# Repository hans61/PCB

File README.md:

# PCB
Gigatron extensions
=======================
Here I collect my PCB (Eagle + Gerber) extensions for the Gigatron TTL computer. You can find the original project here:
https://gigatron.io/

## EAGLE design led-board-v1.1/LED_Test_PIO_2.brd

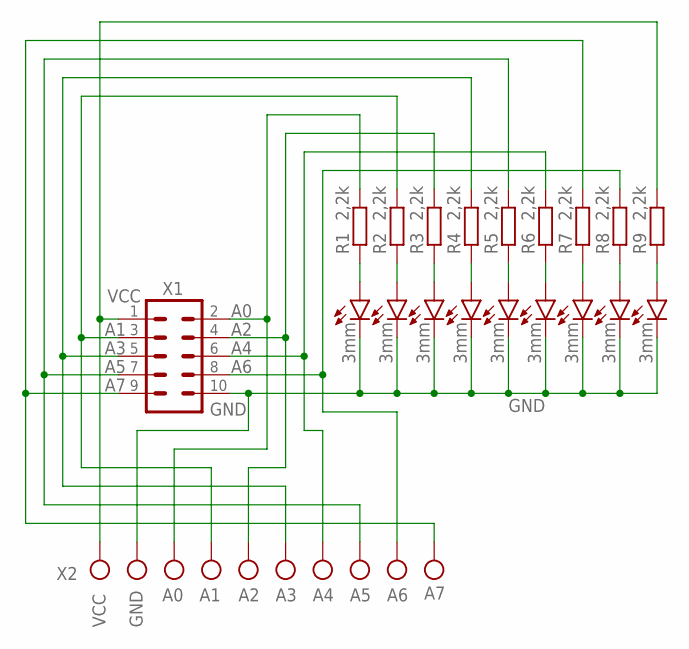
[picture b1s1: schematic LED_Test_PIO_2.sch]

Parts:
LED1, LED2, LED3, LED4, LED5, LED6, LED7, LED8, LED9: 3mm; LED3MM
R1, R2, R3, R4, R5, R6, R7, R8, R9: 2,2k; 0207/10
SV1: X1; ML10
X1, X2, X3, X4, X5: X2; W237-102

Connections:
A0: R1.2, SV1.2, X2.1
A1: R2.2, SV1.3, X2.2
A2: R3.2, SV1.4, X3.1
A3: R4.2, SV1.5, X3.2
A4: R6.2, SV1.6, X4.1
A5: R5.2, SV1.7, X4.2
A6: R8.2, SV1.8, X5.1
A7: R7.2, SV1.9, X5.2
GND: LED1.K (C), LED2.K (C), LED3.K (C), LED4.K (C), LED5.K (C), LED6.K (C), LED7.K (C), LED8.K (C), LED9.K (C), SV1.10, X1.2
unnamed: LED1.A, R1.1
unnamed: LED2.A, R2.1
unnamed: LED3.A, R3.1
unnamed: LED4.A, R4.1
unnamed: LED5.A, R5.1
unnamed: LED6.A, R6.1
unnamed: LED7.A, R7.1
unnamed: LED8.A, R8.1
unnamed: LED9.A, R9.1
VCC: R9.2, SV1.1, X1.1

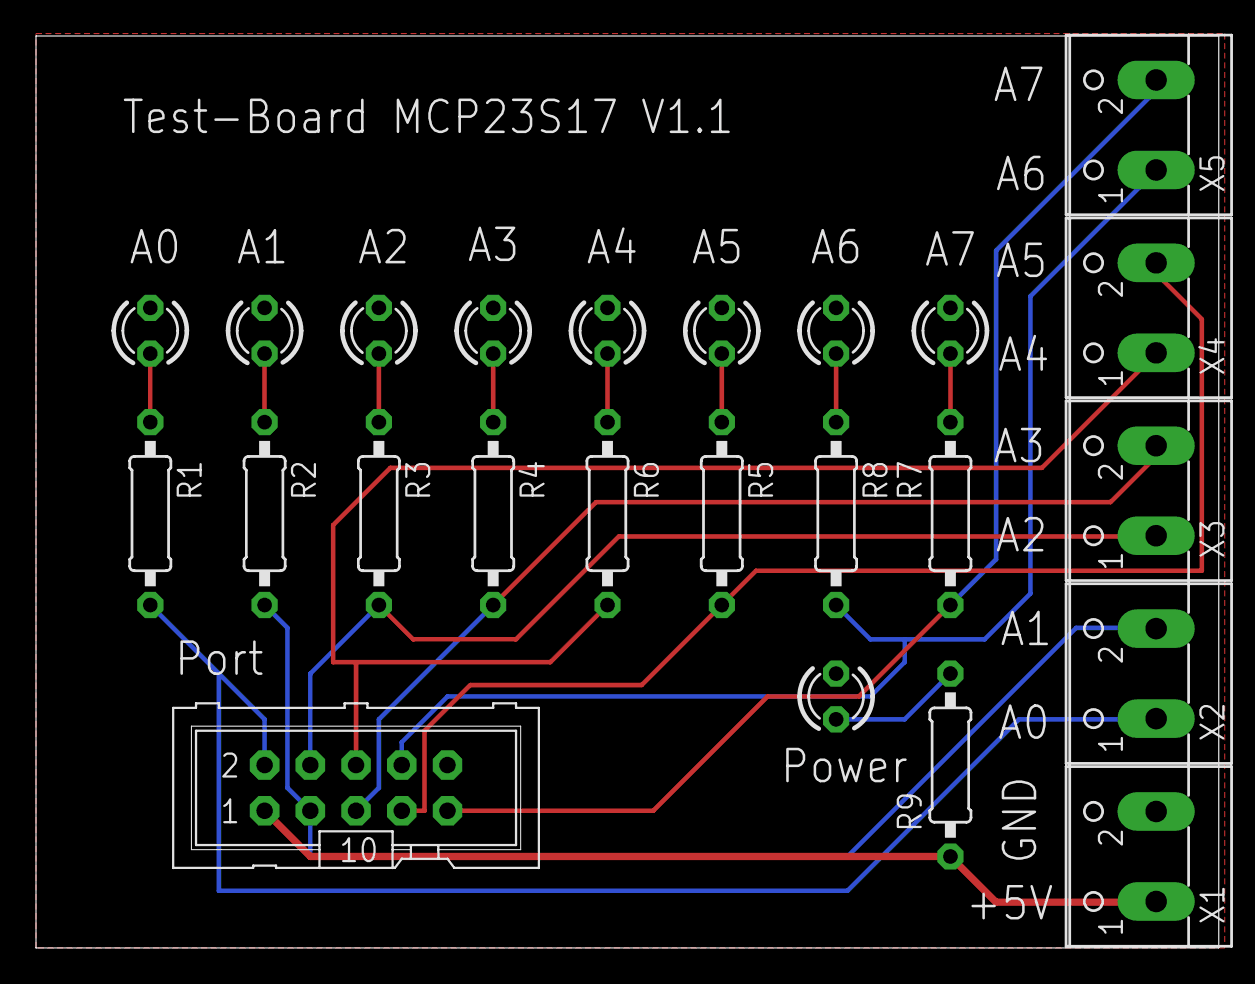
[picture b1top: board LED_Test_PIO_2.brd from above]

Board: 2 copper layers, 65.7 x 50.7 mm, 24 parts (0 on the bottom side), 19 nets.

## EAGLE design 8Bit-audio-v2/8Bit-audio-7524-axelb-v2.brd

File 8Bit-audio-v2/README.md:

8 Bit Audo with the TLC7524
===========================

It is the second draft that tries to avoid the mistakes of the first version. The connection to VREF (15) has been changed. The pin header was adapted to the PCB of lb3361. This means that a 1 to 1 cable can be used. Component footprints have been improved.
! This is just a draft.

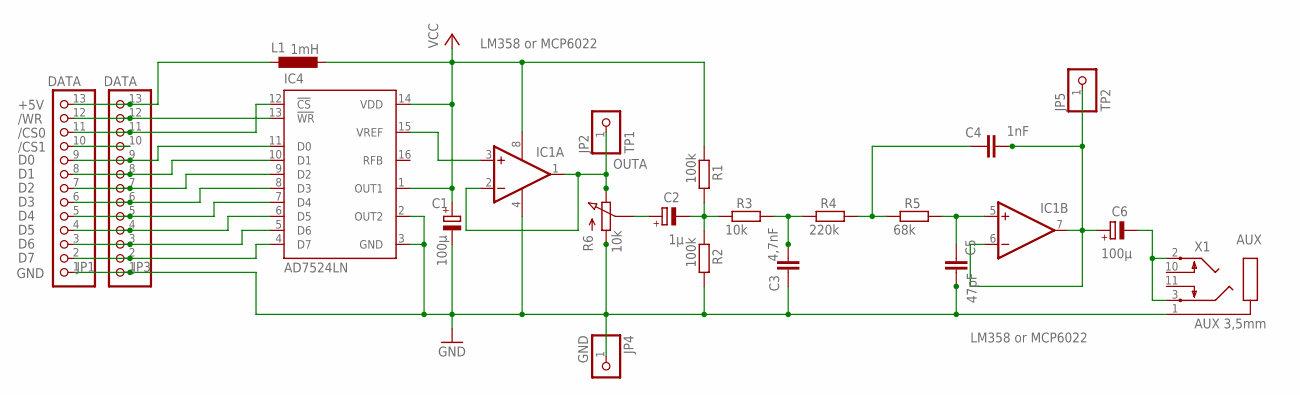
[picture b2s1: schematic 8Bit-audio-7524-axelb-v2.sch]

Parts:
C1, C6: 100µ; E5-5
C2: 1µ; E5-5
C3: 4,7nF; RCL_C025_050-055X075
C4: 1nF; RCL_C025_050-055X075
C5: 47pF; RCL_C025_050-055X075
IC1: LM358 or MCP6022; DIL08
IC4: AD7524LN; DIL16
JP1, JP3: DATA; 1X13
JP2: TP1; 1X01
JP4: GND; 1X01
JP5: TP2; 1X01
L1: 1mH; 0207/10
R1, R2: 100k; 0207/10
R3: 10k; 0207/10
R4: 220k; 0207/10
R5: 68k; 0207/10
R6: 10k; POT_3RP/1610N
X1: AUX 3,5mm; SJ1-352XN

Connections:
+5V: JP1.13, JP3.13, L1.1
/CS0: IC4.12 (!CS), JP1.11, JP3.11
/CS1: JP1.10, JP3.10
/WR: IC4.13 (!WR), JP1.12, JP3.12
AUX: C6.-, X1.2, X1.3
D0: IC4.11 (D0), JP1.9, JP3.9
D1: IC4.10 (D1), JP1.8, JP3.8
D2: IC4.9 (D2), JP1.7, JP3.7
D3: IC4.8 (D3), JP1.6, JP3.6
D4: IC4.7 (D4), JP1.5, JP3.5
D5: IC4.6 (D5), JP1.4, JP3.4
D6: IC4.5 (D6), JP1.3, JP3.3
D7: IC4.4 (D7), JP1.2, JP3.2
GND: C1.-, C3.1 (A1), C5.2 (B1), C5.3 (B2), IC1.4 (V-), IC4.2 (OUT2), IC4.3 (GND), JP1.1, JP3.1, JP4.1, R2.2, R6.A1, R6.A2, X1.1
unnamed: C2.-, R1.2, R2.1, R3.1
unnamed: C2.+, R6.M (S)
unnamed: C3.2 (B1), C3.3 (B2), R3.2, R4.1
unnamed: C4.1 (A1), R4.2, R5.1
unnamed: C5.1 (A1), IC1.5 (+IN), R5.2
OUTA: IC1.1 (OUT), IC1.2 (-IN), JP2.1, R6.E1, R6.E2
OUTB: C4.2 (B1), C4.3 (B2), C6.+, IC1.6 (-IN), IC1.7 (OUT), JP5.1
VCC: C1.+, IC1.8 (V+), IC4.1 (OUT1), IC4.14 (VDD), L1.2, R1.1
VREF: IC1.3 (+IN), IC4.15 (VREF)

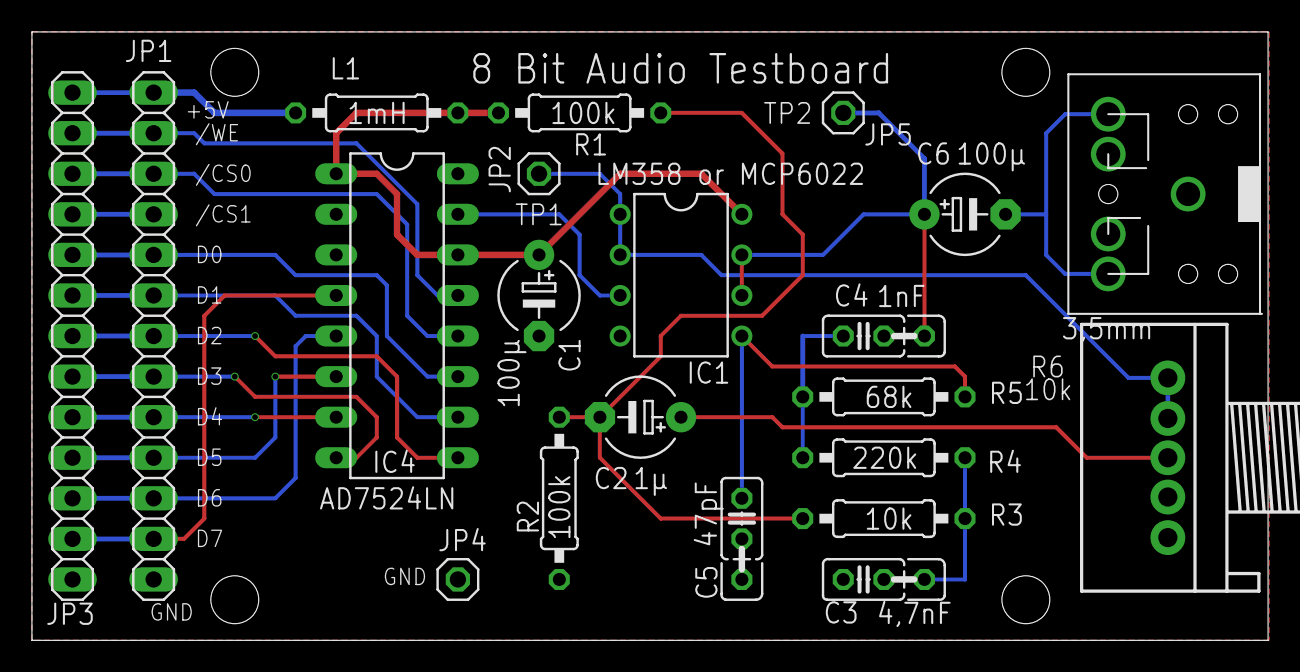
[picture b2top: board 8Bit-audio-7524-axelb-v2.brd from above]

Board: 2 copper layers, 77.4 x 38.1 mm, 21 parts (0 on the bottom side), 23 nets.

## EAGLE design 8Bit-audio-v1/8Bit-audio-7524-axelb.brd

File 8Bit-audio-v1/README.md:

8 Bit Audo with the TLC7524
===========================
This is a small circuit board to test 8 bit audio on the Gigatron. The schematic is from Axelb, thank you very much. Unfortunately I made a mistake. Pin 3 of the MCP6022 is connected to RFB (16). The connection must be separated and a wire must be soldered to VREF (15).
To test the DAC, I first connected it to an Arduino Uno. With the Gigatron it can be connected to the new expansion v7 of lb3361. Many thanks to lb3361 for his work. The following connections must be established:

|Expansion|TLC7524|
|-----------|-----------|
|VCC|+5V|
|/AUXCTRL|/WR|
|/AUXDEV0|/CS|
|A8-A15|D0-D7|
|GND|GND|

In order for the TLC7524 to accept the data, the /WR of GAL1 must be negated.
I changed line 65:

`DEVCLKOUT = !(OE & WE & SPECIALCODE);`

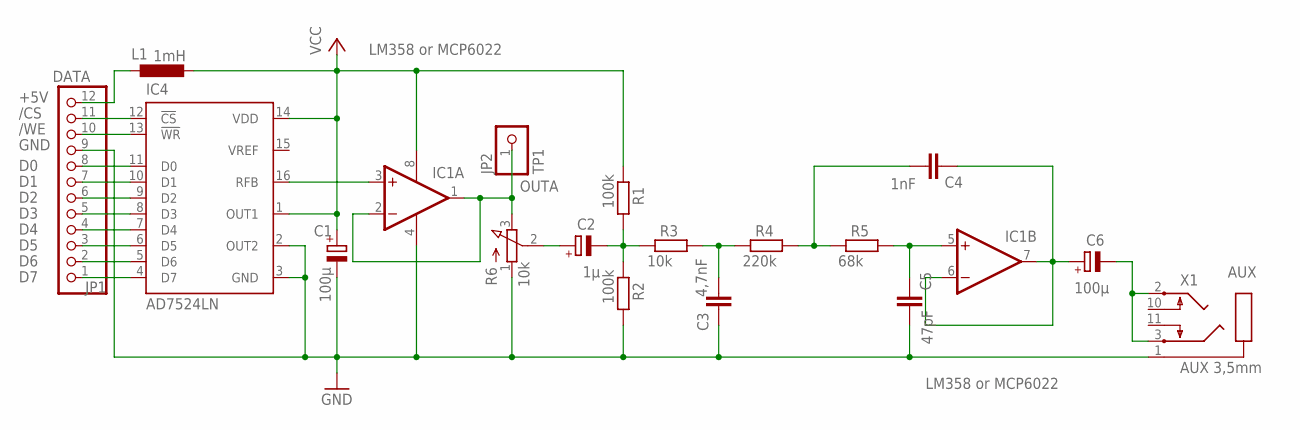
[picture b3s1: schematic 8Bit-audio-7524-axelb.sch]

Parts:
C1, C6: 100µ; E5-5
C2: 1µ; E5-5
C3: 4,7nF; C075-032X103
C4: 1nF; C075-032X103
C5: 47pF; C075-032X103
IC1: LM358 or MCP6022; DIL08
IC4: AD7524LN; DIL16
JP1: DATA; 1X12
JP2: TP1; 1X01
L1: 1mH; 0207/10
R1, R2: 100k; 0207/10
R3: 10k; 0207/10
R4: 220k; 0207/10
R5: 68k; 0207/10
R6: 10k; 3RP/1610N
X1: AUX 3,5mm; SJ1-352XN

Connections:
+5V: JP1.12, L1.1
/CS: IC4.12 (!CS), JP1.11
/WE: IC4.13 (!WR), JP1.10
AUX: C6.-, X1.2, X1.3
D0: IC4.11 (D0), JP1.8
D1: IC4.10 (D1), JP1.7
D2: IC4.9 (D2), JP1.6
D3: IC4.8 (D3), JP1.5
D4: IC4.7 (D4), JP1.4
D5: IC4.6 (D5), JP1.3
D6: IC4.5 (D6), JP1.2
D7: IC4.4 (D7), JP1.1
GND: C1.-, C3.1, C5.2, IC1.4 (V-), IC4.2 (OUT2), IC4.3 (GND), JP1.9, R2.2, R6.1 (A), X1.1
unnamed: IC1.3 (+IN), IC4.16 (RFB)
unnamed: C2.-, R1.2, R2.1, R3.1
unnamed: C2.+, R6.2 (S)
unnamed: C3.2, R3.2, R4.1
unnamed: C4.2, R4.2, R5.1
unnamed: C5.1, IC1.5 (+IN), R5.2
OUTA: IC1.1 (OUT), IC1.2 (-IN), JP2.1, R6.3 (E)
OUTB: C4.1, C6.+, IC1.6 (-IN), IC1.7 (OUT)
VCC: C1.+, IC1.8 (V+), IC4.1 (OUT1), IC4.14 (VDD), L1.2, R1.1

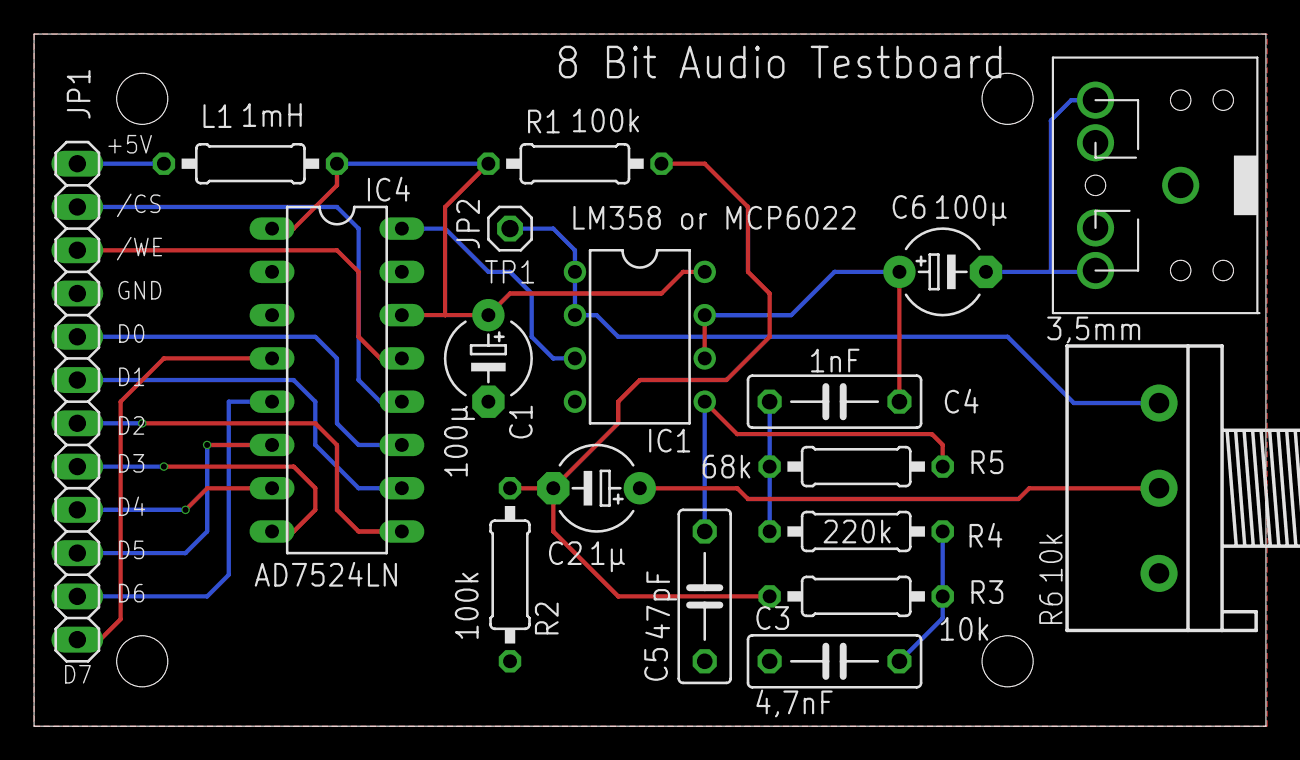
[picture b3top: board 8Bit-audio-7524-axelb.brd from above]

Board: 2 copper layers, 72.3 x 40.6 mm, 18 parts (0 on the bottom side), 22 nets.

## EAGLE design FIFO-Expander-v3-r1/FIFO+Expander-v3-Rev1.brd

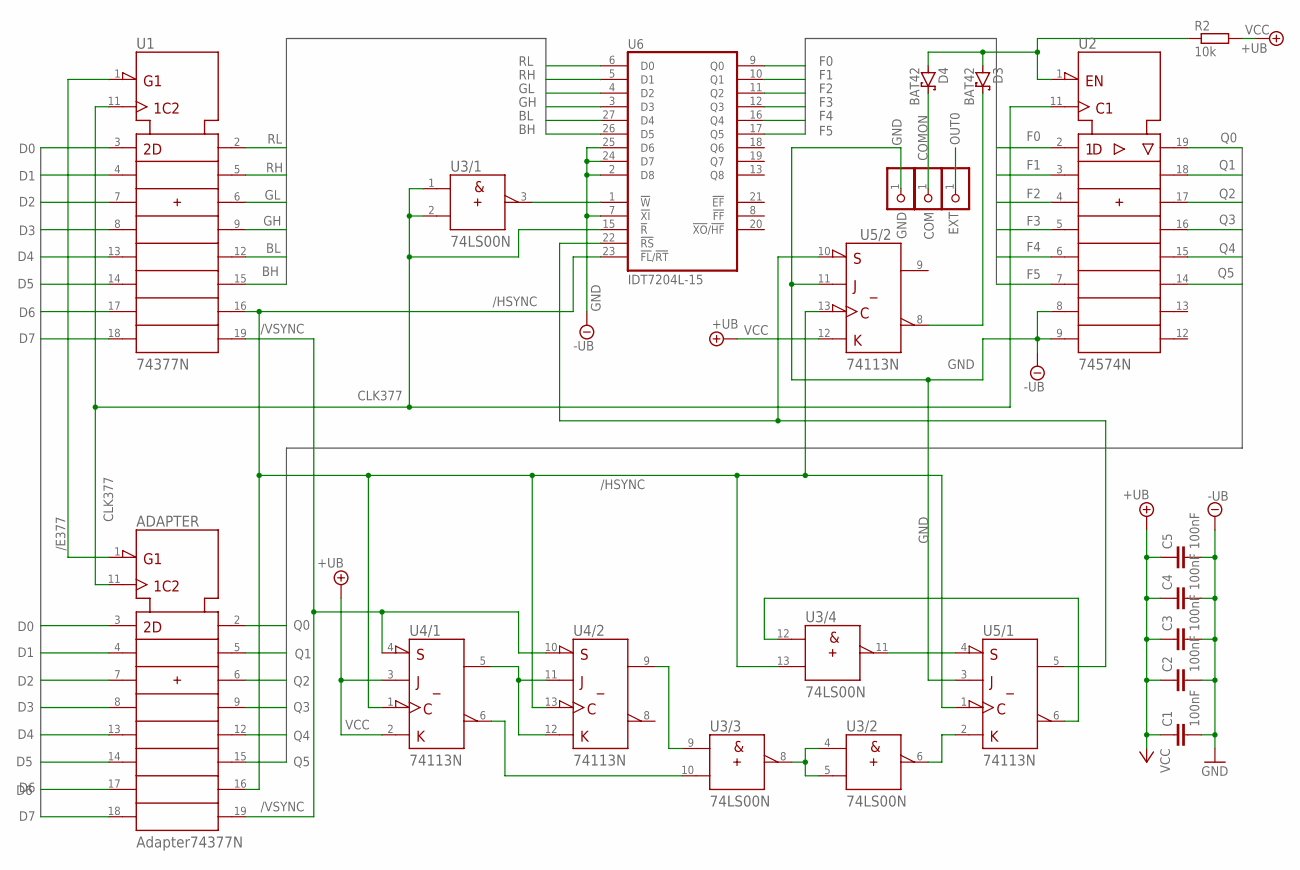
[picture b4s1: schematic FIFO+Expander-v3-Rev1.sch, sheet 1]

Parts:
ADAPTER: Adapter74377N; DIL20
C1, C2, C3, C4, C5: 100nF; C5B2.5
COMON: COM; 1X01
D3, D4: BAT42; DO35-10
GND: GND; 1X01
OUT0: EXT; 1X01
R2: 10k; 0207/10
U1: 74377N; DIL20
U2: 74574N; DIL20
U3: 74LS00N; DIL14
U4, U5: 74113N; DIL14
U6: IDT7204L-15; DIL28-3

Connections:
/E377: ADAPTER.1 (!G), U1.1 (!G)
/HSYNC: ADAPTER.16 (7Q), U1.16 (7Q), U3.13 (B), U4.1 (CLK), U4.13 (CLK), U5.1 (CLK), U5.13 (CLK), U6.23 (!FL!/!RT)
/VSYNC: ADAPTER.19 (8Q), U1.19 (8Q), U4.4 (!PRE), U4.10 (!PRE)
BH: U1.15 (6Q), U6.26 (D5)
BL: U1.12 (5Q), U6.27 (D4)
CLK377: ADAPTER.11 (CLK), U1.11 (CLK), U2.11 (CLK), U3.1 (A), U3.2 (B), U6.15 (!R)
D0: ADAPTER.3 (1D), U1.3 (1D)
D1: ADAPTER.4 (2D), U1.4 (2D)
D2: ADAPTER.7 (3D), U1.7 (3D)
D3: ADAPTER.8 (4D), U1.8 (4D)
D4: ADAPTER.13 (5D), U1.13 (5D)
D5: ADAPTER.14 (6D), U1.14 (6D)
D6: ADAPTER.17 (7D), U1.17 (7D)
D7: ADAPTER.18 (8D), U1.18 (8D)
F0: U2.2 (1D), U6.9 (Q0)
F1: U2.3 (2D), U6.10 (Q1)
F2: U2.4 (3D), U6.11 (Q2)
F3: U2.5 (4D), U6.12 (Q3)
F4: U2.6 (5D), U6.16 (Q4)
F5: U2.7 (6D), U6.17 (Q5)
GH: U1.9 (4Q), U6.3 (D3)
GL: U1.6 (3Q), U6.4 (D2)
GND: ADAPTER.10 (-UB), C1.2, C2.2, C3.2, C4.2, C5.2, GND.1, U1.10 (-UB), U2.8 (7D), U2.9 (8D), U2.10 (-UB), U3.7 (-UB), U4.7 (-UB), U5.3 (J), U5.7 (-UB), U5.11 (J), U6.2 (D8), U6.7 (!XI), U6.14 (GND), U6.24 (D7), U6.25 (D6); also elsewhere on the board
unnamed: U4.5 (Q), U4.11 (J), U4.12 (K)
unnamed: U3.3 (Y), U6.1 (!W)
unnamed: U3.10 (B), U4.6 (!Q)
unnamed: U3.9 (A), U4.9 (Q)
unnamed: D3.A, D4.A, R2.1, U2.1 (!OC)
unnamed: U3.4 (A), U3.5 (B), U3.8 (Y)
unnamed: U3.6 (Y), U5.2 (K)
unnamed: U3.11 (Y), U5.4 (!PRE)
unnamed: U3.12 (A), U5.6 (!Q)
unnamed: COMON.1, D4.C
unnamed: D3.C, U5.8 (!Q)
unnamed: U5.5 (Q), U5.10 (!PRE), U6.22 (!RS)
OUT0: OUT0.1; also elsewhere on the board
Q0: ADAPTER.2 (1Q), U2.19 (1Q)
Q1: ADAPTER.5 (2Q), U2.18 (2Q)
Q2: ADAPTER.6 (3Q), U2.17 (3Q)
Q3: ADAPTER.9 (4Q), U2.16 (4Q)
Q4: ADAPTER.12 (5Q), U2.15 (5Q)
Q5: ADAPTER.15 (6Q), U2.14 (6Q)
RH: U1.5 (2Q), U6.5 (D1)
RL: U1.2 (1Q), U6.6 (D0)
VCC: ADAPTER.20 (+UB), C1.1, C2.1, C3.1, C4.1, C5.1, R2.2, U1.20 (+UB), U2.20 (+UB), U3.14 (+UB), U4.2 (K), U4.3 (J), U4.14 (+UB), U5.12 (K), U5.14 (+UB), U6.28 (VCC); also elsewhere on the board

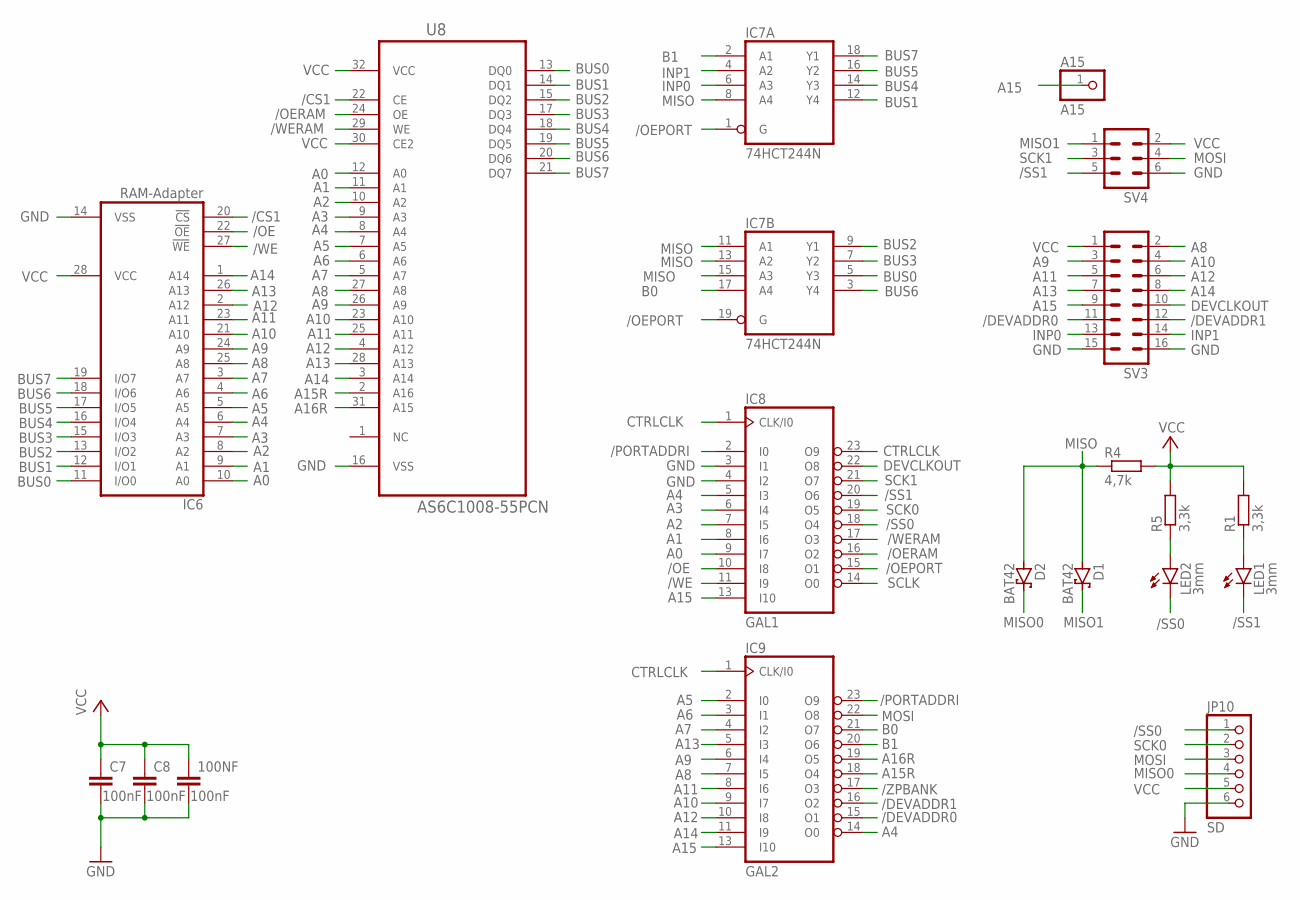
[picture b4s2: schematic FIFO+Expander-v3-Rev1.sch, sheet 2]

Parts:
100NF: 100nF; C5B2.5
A15: A15; 1X01
C7, C8: 100nF; C5B2.5
D1, D2: BAT42; DO35-10
IC6: RAM-Adapter; DIL28-6
IC7: 74HCT244N; DIL20
IC8: GAL1; DIL24-3
IC9: GAL2; DIL24-3
JP10: SD; 1X06
LED1, LED2: 3mm; LED3MM
R1, R5: 3,3k; 0207/10
R4: 4,7k; 0207/10
SV3: ML16
SV4: ML6
U8: AS6C1008-55PCN; DIP254P1524X393-32

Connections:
/CS1: IC6.20 (!CS), U8.22 (CE)
/DEVADDR0: IC9.15 (O1), SV3.11; also elsewhere on the board
/DEVADDR1: IC9.16 (O2), SV3.12
/OE: IC6.22 (!OE), IC8.10 (I8)
/OEPORT: IC7.1 (G), IC7.19 (G), IC8.15 (O1)
/OERAM: IC8.16 (O2), U8.24 (OE)
/PORTADDRI: IC8.2 (I0), IC9.23 (O9)
/SS0: IC8.18 (O4), JP10.1, LED2.K (C)
/SS1: IC8.20 (O6), LED1.K (C), SV4.5
/WE: IC6.27 (!WE), IC8.11 (I9)
/WERAM: IC8.17 (O3), U8.29 (WE)
/ZPBANK: IC9.17 (O3)
A0: IC6.10 (A0), IC8.9 (I7), U8.12 (A0)
A1: IC6.9 (A1), IC8.8 (I6), U8.11 (A1)
A2: IC6.8 (A2), IC8.7 (I5), U8.10 (A2)
A3: IC6.7 (A3), IC8.6 (I4), U8.9 (A3)
A4: IC6.6 (A4), IC8.5 (I3), IC9.14 (O0), U8.8 (A4)
A5: IC6.5 (A5), IC9.2 (I0), U8.7 (A5)
A6: IC6.4 (A6), IC9.3 (I1), U8.6 (A6)
A7: IC6.3 (A7), IC9.4 (I2), U8.5 (A7)
A8: IC6.25 (A8), IC9.7 (I5), SV3.2, U8.27 (A8); also elsewhere on the board
A9: IC6.24 (A9), IC9.6 (I4), SV3.3, U8.26 (A9); also elsewhere on the board
A10: IC6.21 (A10), IC9.9 (I7), SV3.4, U8.23 (A10); also elsewhere on the board
A11: IC6.23 (A11), IC9.8 (I6), SV3.5, U8.25 (A11); also elsewhere on the board
A12: IC6.2 (A12), IC9.10 (I8), SV3.6, U8.4 (A12); also elsewhere on the board
A13: IC6.26 (A13), IC9.5 (I3), SV3.7, U8.28 (A13); also elsewhere on the board
A14: IC6.1 (A14), IC9.11 (I9), SV3.8, U8.3 (A14); also elsewhere on the board
A15: A15.1, IC8.13 (I10), IC9.13 (I10), SV3.9; also elsewhere on the board
A15R: IC9.18 (O4), U8.2 (A16)
A16R: IC9.19 (O5), U8.31 (A15)
B0: IC7.17 (A4), IC9.21 (O7)
B1: IC7.2 (A1), IC9.20 (O6)
BUS0: IC6.11 (I/O0), IC7.5 (Y3), U8.13 (DQ0)
BUS1: IC6.12 (I/O1), IC7.12 (Y4), U8.14 (DQ1)
BUS2: IC6.13 (I/O2), IC7.9 (Y1), U8.15 (DQ2)
BUS3: IC6.15 (I/O3), IC7.7 (Y2), U8.17 (DQ3)
BUS4: IC6.16 (I/O4), IC7.14 (Y3), U8.18 (DQ4)
BUS5: IC6.17 (I/O5), IC7.16 (Y2), U8.19 (DQ5)
BUS6: IC6.18 (I/O6), IC7.3 (Y4), U8.20 (DQ6)
BUS7: IC6.19 (I/O7), IC7.18 (Y1), U8.21 (DQ7)
CTRLCLK: IC8.1 (CLK/I0), IC8.23 (O9), IC9.1 (CLK/I0)
DEVCLKOUT: IC8.22 (O8), SV3.10; also elsewhere on the board
GND: 100NF.2, C7.2, C8.2, IC6.14 (VSS), IC7.10 (GND), IC8.3 (I1), IC8.4 (I2), IC8.12 (GND), IC9.12 (GND), JP10.6, SV3.15, SV3.16, SV4.6, U8.16 (VSS); also elsewhere on the board
INP0: IC7.6 (A3), SV3.13
INP1: IC7.4 (A2), SV3.14
MISO: D1.A, D2.A, IC7.8 (A4), IC7.11 (A1), IC7.13 (A2), IC7.15 (A3), R4.1
MISO0: D2.C, JP10.4
MISO1: D1.C, SV4.1
MOSI: IC9.22 (O8), JP10.3, SV4.4
unnamed: LED2.A, R5.1
unnamed: LED1.A, R1.1
SCK0: IC8.19 (O5), JP10.2
SCK1: IC8.21 (O7), SV4.3
SCLK: IC8.14 (O0)
VCC: 100NF.1, C7.1, C8.1, IC6.28 (VCC), IC7.20 (VCC), IC8.24 (VCC), IC9.24 (VCC), JP10.5, R1.2, R4.2, R5.2, SV3.1, SV4.2, U8.30 (CE2), U8.32 (VCC); also elsewhere on the board

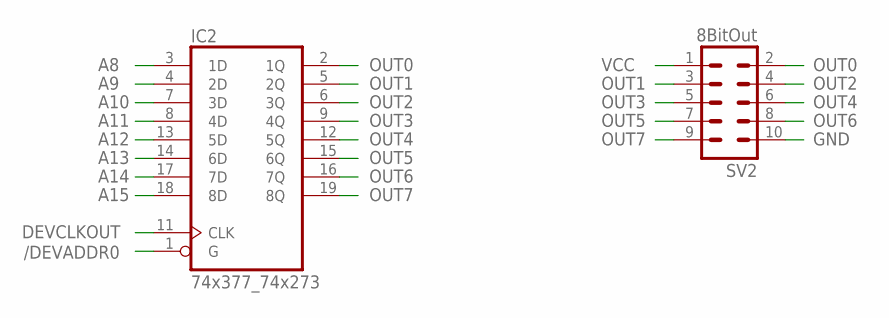
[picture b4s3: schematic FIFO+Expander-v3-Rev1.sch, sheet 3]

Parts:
IC2: 74x377_74x273; DIL20
SV2: 8BitOut; ML10

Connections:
/DEVADDR0: IC2.1 (G); also elsewhere on the board
A8: IC2.3 (1D); also elsewhere on the board
A9: IC2.4 (2D); also elsewhere on the board
A10: IC2.7 (3D); also elsewhere on the board
A11: IC2.8 (4D); also elsewhere on the board
A12: IC2.13 (5D); also elsewhere on the board
A13: IC2.14 (6D); also elsewhere on the board
A14: IC2.17 (7D); also elsewhere on the board
A15: IC2.18 (8D); also elsewhere on the board
DEVCLKOUT: IC2.11 (CLK); also elsewhere on the board
GND: IC2.10 (GND), SV2.10; also elsewhere on the board
OUT0: IC2.2 (1Q), SV2.2; also elsewhere on the board
OUT1: IC2.5 (2Q), SV2.3
OUT2: IC2.6 (3Q), SV2.4
OUT3: IC2.9 (4Q), SV2.5
OUT4: IC2.12 (5Q), SV2.6
OUT5: IC2.15 (6Q), SV2.7
OUT6: IC2.16 (7Q), SV2.8
OUT7: IC2.19 (8Q), SV2.9
VCC: IC2.20 (VCC), SV2.1; also elsewhere on the board

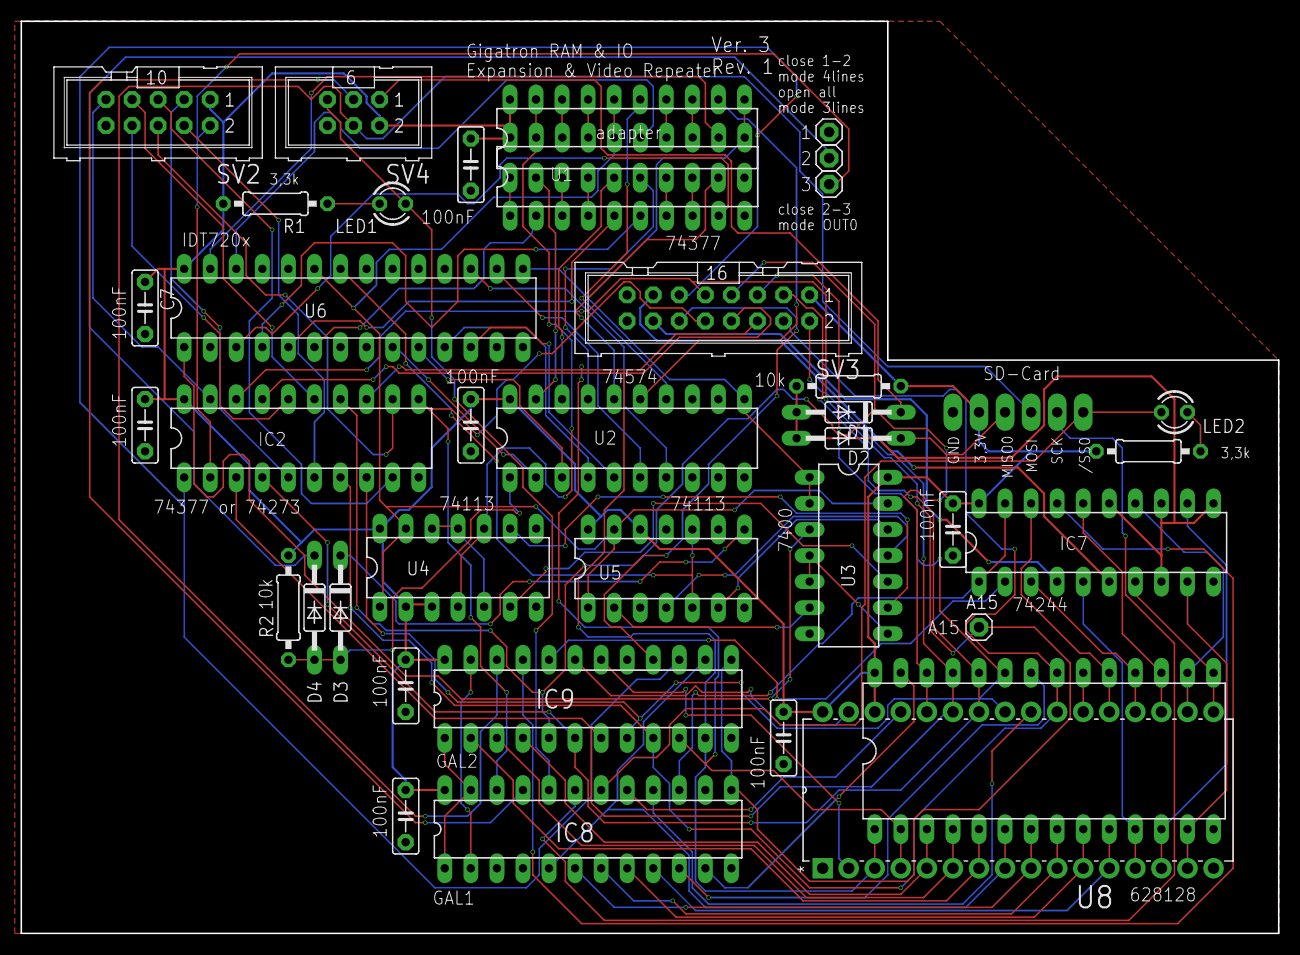
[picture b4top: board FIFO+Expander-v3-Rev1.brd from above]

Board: 2 copper layers, 122.6 x 88.9 mm, 39 parts (1 on the bottom side), 103 nets.

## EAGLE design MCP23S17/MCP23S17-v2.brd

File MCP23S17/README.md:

External MCP23S17 test board
============================
It's a small PCB with the MCP23S17 (SPI I/O extension). It has 16 LEDs on both 8 bit ports. The ports are brought out on 2x5 pin headers and the SPI bus with power supply is connected via 2x3 pin headers. The pin assignment is compatible with the original extension. Important!!! When operating on the Gigatron, the 10k pull-up resistor must not be fitted.

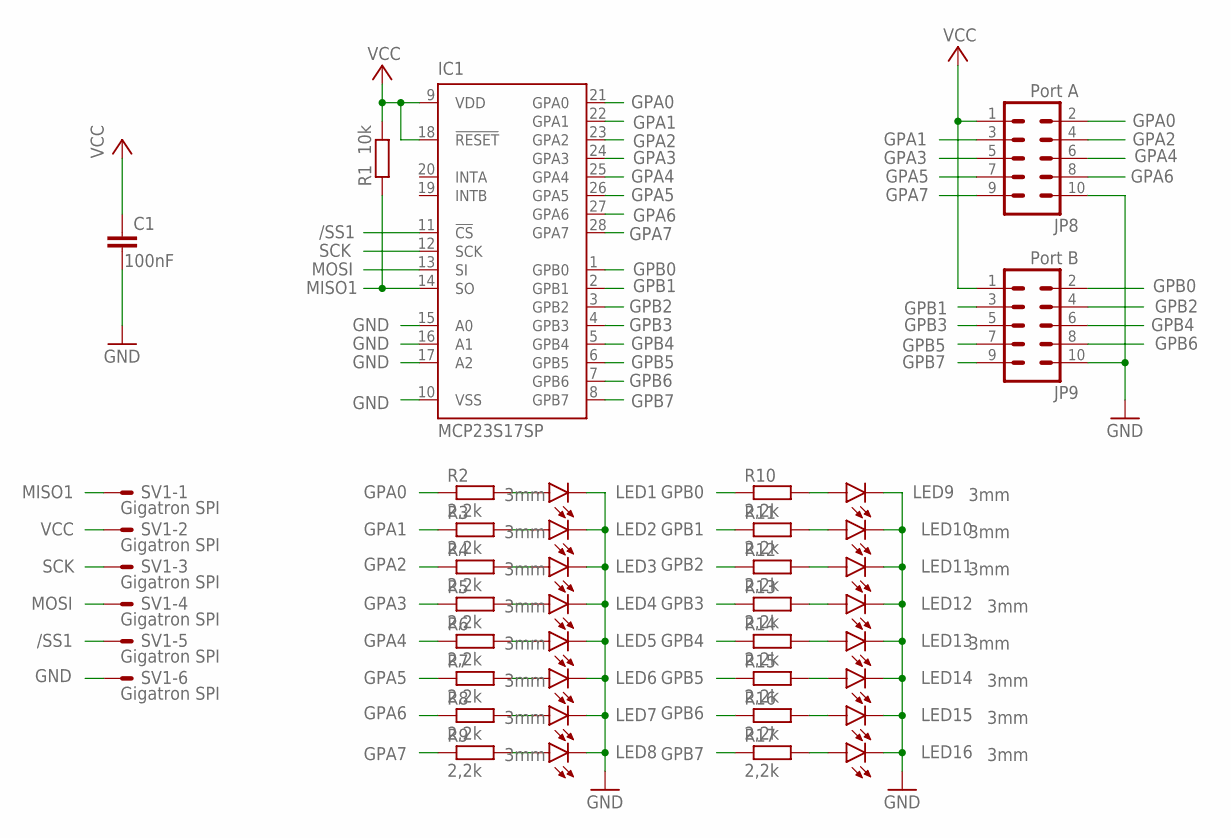
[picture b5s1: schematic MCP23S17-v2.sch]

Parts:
C1: 100nF; C5B2.5
IC1: MCP23S17SP; DIL28-3
JP8: Port A; ML10
JP9: Port B; ML10
LED1, LED2, LED3, LED4, LED5, LED6, LED7, LED8, LED9, LED10, LED11, LED12, LED13, LED14, LED15, LED16: 3mm; LED3MM
R1: 10k; 0207/10
R2, R3, R4, R5, R6, R7, R8, R9, R10, R11, R12, R13, R14, R15, R16, R17: 2,2k; 0207/10
SV1: Gigatron SPI; ML6

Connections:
/SS1: IC1.11 (!CS), SV1.5
GND: C1.2, IC1.10 (VSS), IC1.15 (A0), IC1.16 (A1), IC1.17 (A2), JP8.10, JP9.10, LED1.K (C), LED2.K (C), LED3.K (C), LED4.K (C), LED5.K (C), LED6.K (C), LED7.K (C), LED8.K (C), LED9.K (C), LED10.K (C), LED11.K (C), LED12.K (C), LED13.K (C), LED14.K (C), LED15.K (C), LED16.K (C), SV1.6
GPA0: IC1.21 (GPA0), JP8.2, R2.1
GPA1: IC1.22 (GPA1), JP8.3, R3.1
GPA2: IC1.23 (GPA2), JP8.4, R4.1
GPA3: IC1.24 (GPA3), JP8.5, R5.1
GPA4: IC1.25 (GPA4), JP8.6, R6.1
GPA5: IC1.26 (GPA5), JP8.7, R7.1
GPA6: IC1.27 (GPA6), JP8.8, R8.1
GPA7: IC1.28 (GPA7), JP8.9, R9.1
GPB0: IC1.1 (GPB0), JP9.2, R10.1
GPB1: IC1.2 (GPB1), JP9.3, R11.1
GPB2: IC1.3 (GPB2), JP9.4, R12.1
GPB3: IC1.4 (GPB3), JP9.5, R13.1
GPB4: IC1.5 (GPB4), JP9.6, R14.1
GPB5: IC1.6 (GPB5), JP9.7, R15.1
GPB6: IC1.7 (GPB6), JP9.8, R16.1
GPB7: IC1.8 (GPB7), JP9.9, R17.1
MISO1: IC1.14 (SO), R1.1, SV1.1
MOSI: IC1.13 (SI), SV1.4
unnamed: LED1.A, R2.2
unnamed: LED2.A, R3.2
unnamed: LED3.A, R4.2
unnamed: LED4.A, R5.2
unnamed: LED5.A, R6.2
unnamed: LED6.A, R7.2
unnamed: LED7.A, R8.2
unnamed: LED8.A, R9.2
unnamed: LED9.A, R10.2
unnamed: LED10.A, R11.2
unnamed: LED11.A, R12.2
unnamed: LED12.A, R13.2
unnamed: LED13.A, R14.2
unnamed: LED14.A, R15.2
unnamed: LED15.A, R16.2
unnamed: LED16.A, R17.2
SCK: IC1.12 (SCK), SV1.3
VCC: C1.1, IC1.9 (VDD), IC1.18 (!RESET), JP8.1, JP9.1, R1.2, SV1.2

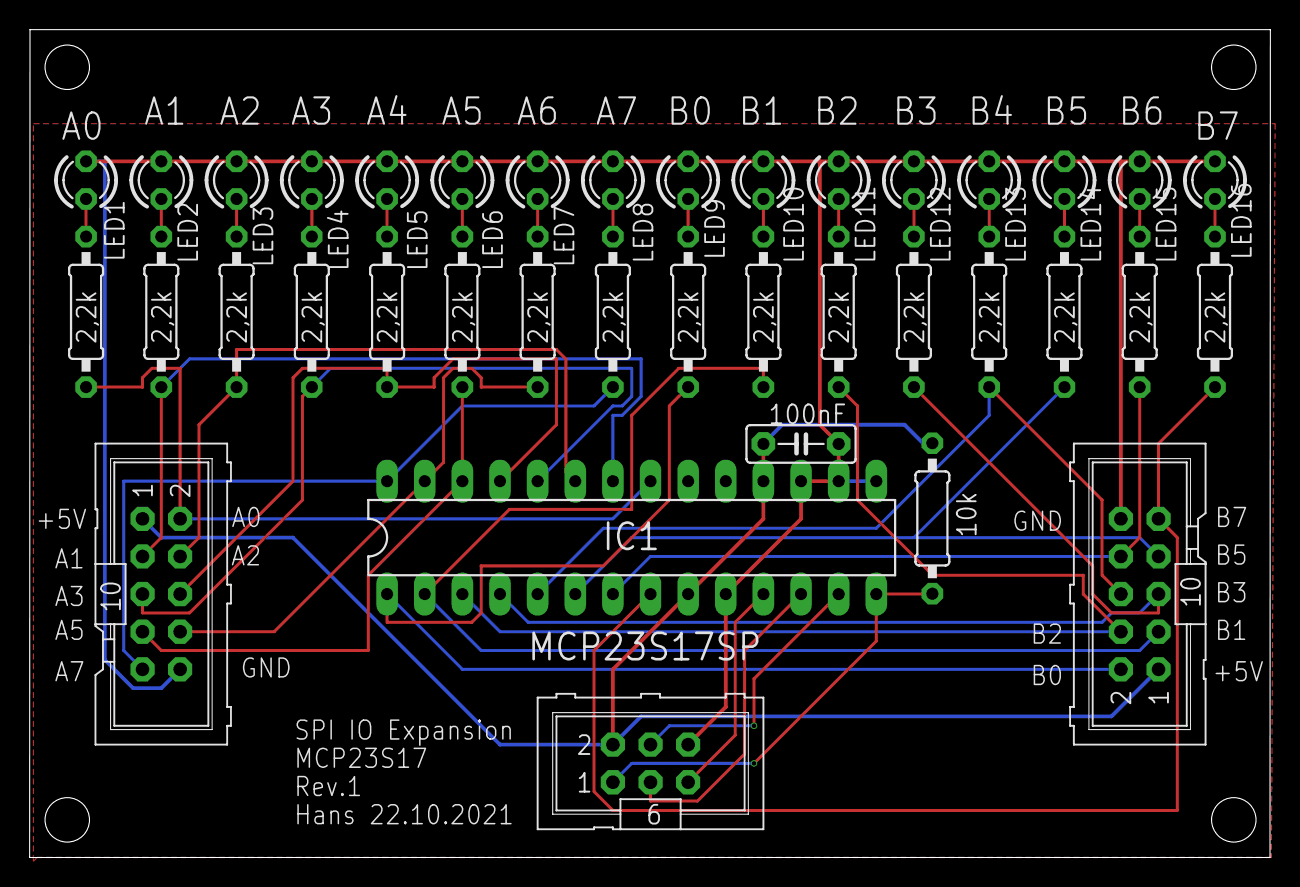
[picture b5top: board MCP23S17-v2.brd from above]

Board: 2 copper layers, 83.7 x 55.9 mm, 38 parts (0 on the bottom side), 38 nets.

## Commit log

2021-11-10 Rename read.me to README.md
2021-12-09 New footprints
2022-05-23 Adapter added
